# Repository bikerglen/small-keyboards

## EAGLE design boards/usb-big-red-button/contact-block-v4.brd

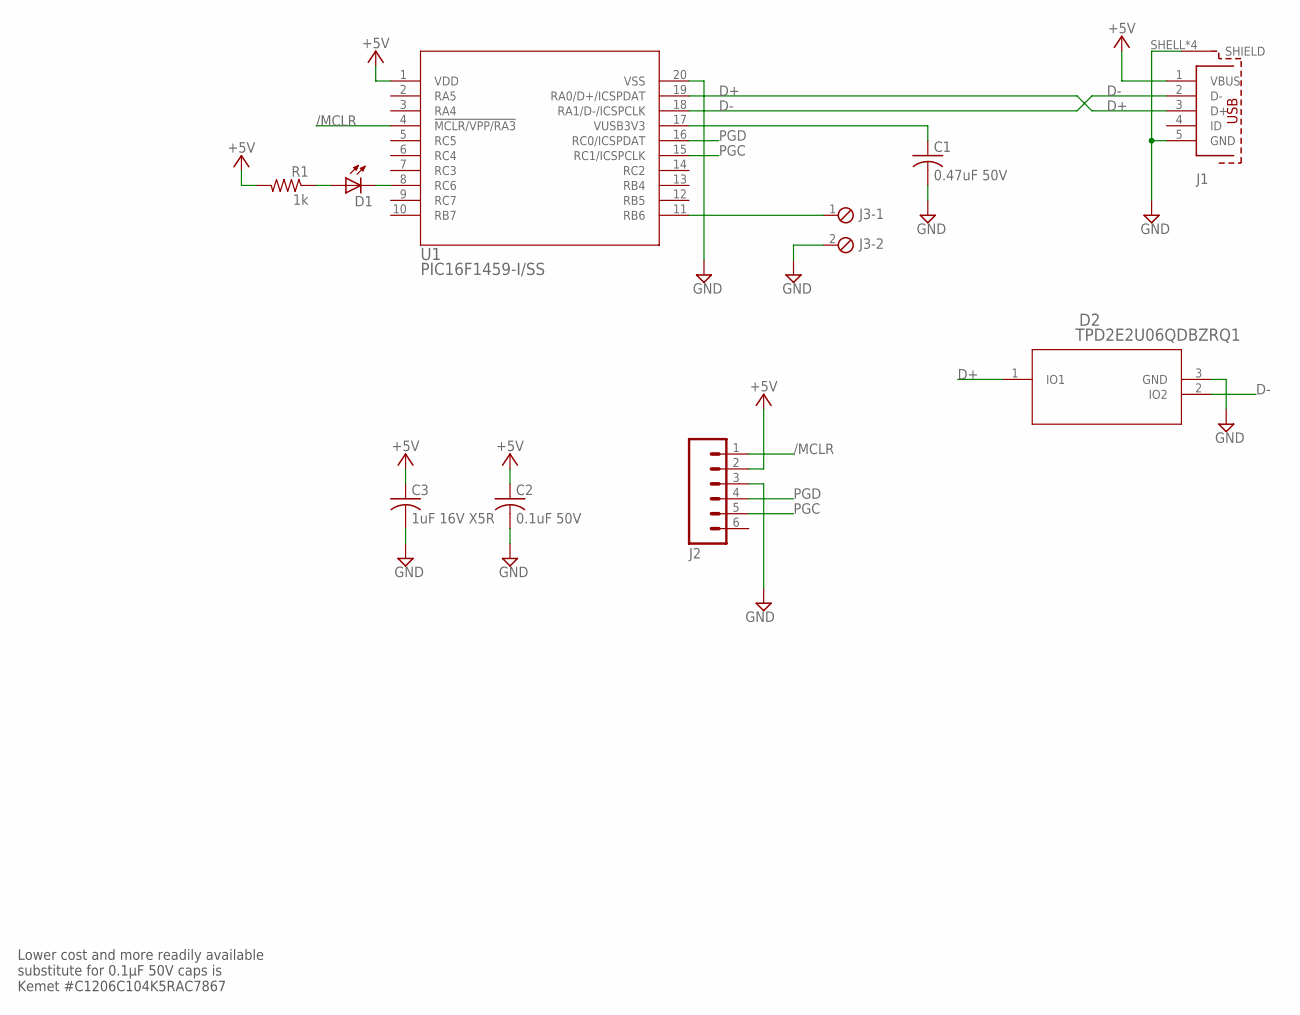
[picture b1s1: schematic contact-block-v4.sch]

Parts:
C1: 0.47uF 50V; C1206K; MFR_PART_NO C1206C474K5RACTU
C2: 0.1uF 50V; C1206K; MFR_PART_NO C1206S104M5RACTU
C3: 1uF 16V X5R; C1210; MFR_PART_NO C1210C105K4PACTU
D1: LEDKA-3528ASYC; KA-3528ASYC
D2: TPD2E2U06QDBZRQ1; DBZ3
J1: 629105136821
J2: M06SIP; 1X06
J3: MPT2; 2POL254
R1: 1k; R1206; MFR_PART_NO CR1206-JW-102ELF
U1: PIC16F1459-I/SS; SSOP20_MC

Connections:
+5V: C2.1, C3.1, J1.1 (VBUS), J2.2, R1.2, U1.1 (VDD)
/MCLR: J2.1, U1.4 (!MCLR/VPP/RA3)
D+: D2.1 (IO1), J1.3 (D+), U1.19 (RA0/D+/ICSPDAT)
D-: D2.2 (IO2), J1.2 (D-), U1.18 (RA1/D-/ICSPCLK)
GND: C1.2, C2.2, C3.2, D2.3 (GND), J1.5 (GND), J1.SHELL (SHIELD), J1.SHELL1 (SHIELD), J1.SHELL2 (SHIELD), J1.SHELL3 (SHIELD), J2.3, J3.2, U1.20 (VSS)
unnamed: D1.A, R1.1
PGC: J2.5, U1.15 (RC1/ICSPCLK)
PGD: J2.4, U1.16 (RC0/ICSPDAT)
RB6: J3.1, U1.11 (RB6)
RC6: D1.C, U1.8 (RC6)
VUSB: C1.1, U1.17 (VUSB3V3)

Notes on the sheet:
Lower cost and more readily available substitute for 0.1µF 50V caps is Kemet #C1206C104K5RAC7867

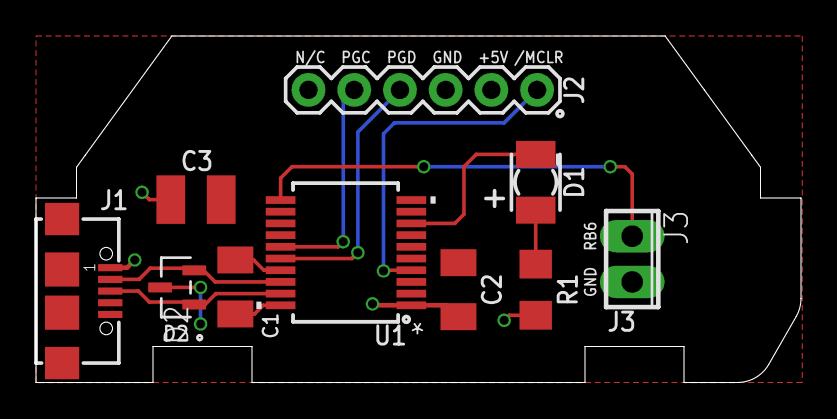
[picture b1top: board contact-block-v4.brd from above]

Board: 2 copper layers, 42.5 x 19.2 mm, 10 parts (0 on the bottom side), 11 nets.

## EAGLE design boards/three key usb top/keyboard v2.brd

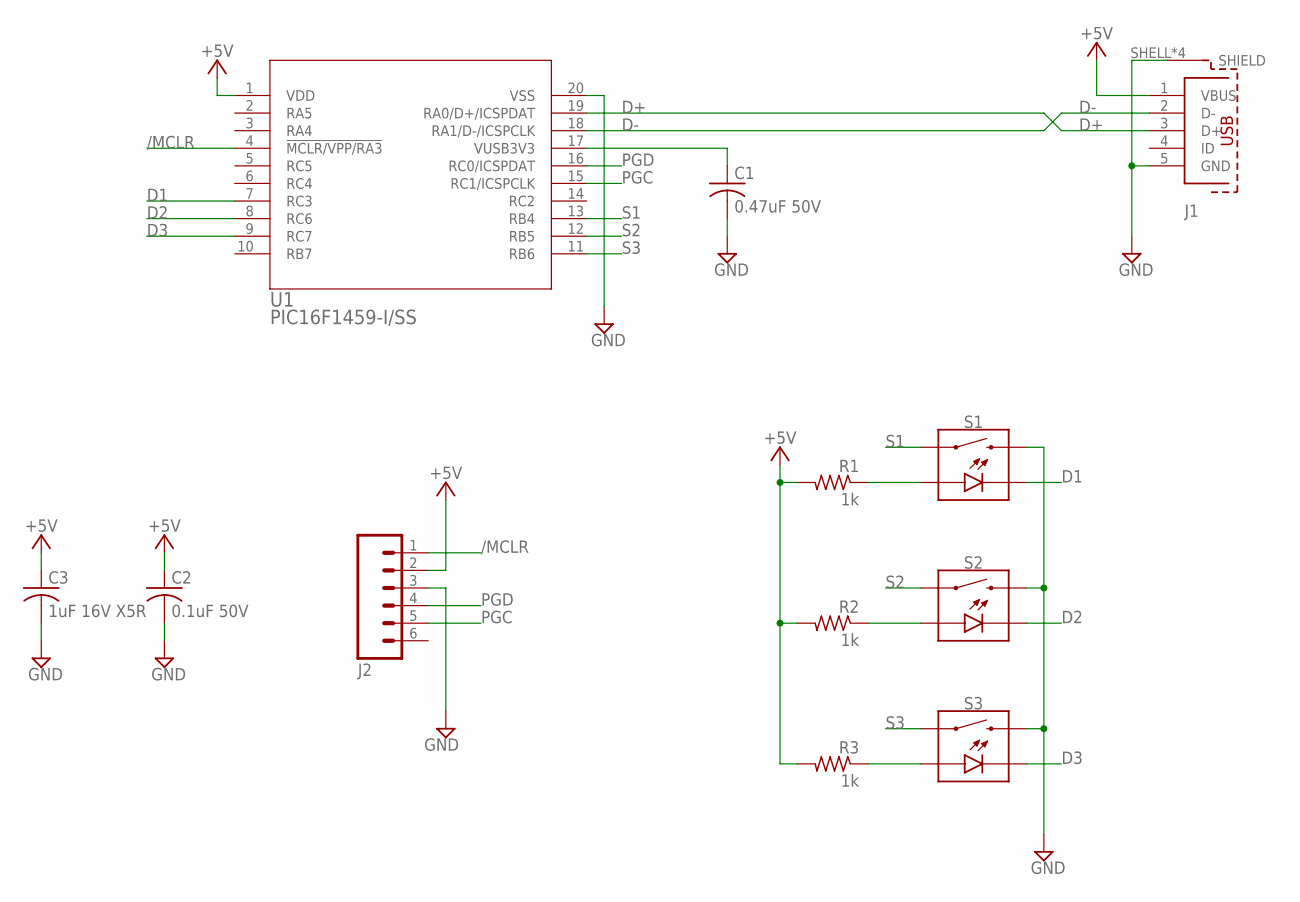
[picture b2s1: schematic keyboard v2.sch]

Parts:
C1: 0.47uF 50V; C1206K; MFR_PART_NO C1206C474K5RACTU
C2: 0.1uF 50V; C1206K; MFR_PART_NO C1206S104M5RACTU
C3: 1uF 16V X5R; C1210; MFR_PART_NO C1210C105K4PACTU
J1: 629105136821
J2: M06SIP; 1X06
R1, R2, R3: 1k; R1206; MFR_PART_NO CR1206-JW-102ELF
S1, S2, S3: MOMENTARY-SWITCH-SPST-LED-PTH-CHERRY; CHERRY-MX-LED
U1: PIC16F1459-I/SS; SSOP20_MC

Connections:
+5V: C2.1, C3.1, J1.1 (VBUS), J2.2, R1.2, R2.2, R3.2, U1.1 (VDD)
/MCLR: J2.1, U1.4 (!MCLR/VPP/RA3)
D1: S1.K (C), U1.7 (RC3)
D2: S2.K (C), U1.8 (RC6)
D3: S3.K (C), U1.9 (RC7)
D+: J1.3 (D+), U1.19 (RA0/D+/ICSPDAT)
D-: J1.2 (D-), U1.18 (RA1/D-/ICSPCLK)
GND: C1.2, C2.2, C3.2, J1.5 (GND), J1.SHELL (SHIELD), J1.SHELL1 (SHIELD), J1.SHELL2 (SHIELD), J1.SHELL3 (SHIELD), J2.3, S1.S2 (2), S2.S2 (2), S3.S2 (2), U1.20 (VSS)
unnamed: R1.1, S1.A
unnamed: R2.1, S2.A
unnamed: R3.1, S3.A
PGC: J2.5, U1.15 (RC1/ICSPCLK)
PGD: J2.4, U1.16 (RC0/ICSPDAT)
S1: S1.S1 (1), U1.13 (RB4)
S2: S2.S1 (1), U1.12 (RB5)
S3: S3.S1 (1), U1.11 (RB6)
VUSB: C1.1, U1.17 (VUSB3V3)

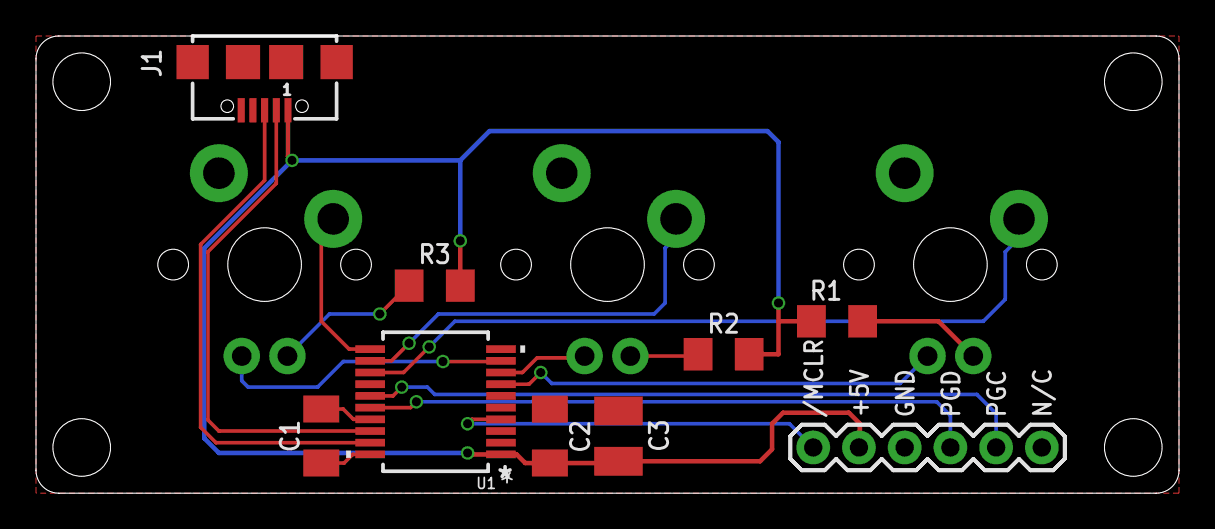
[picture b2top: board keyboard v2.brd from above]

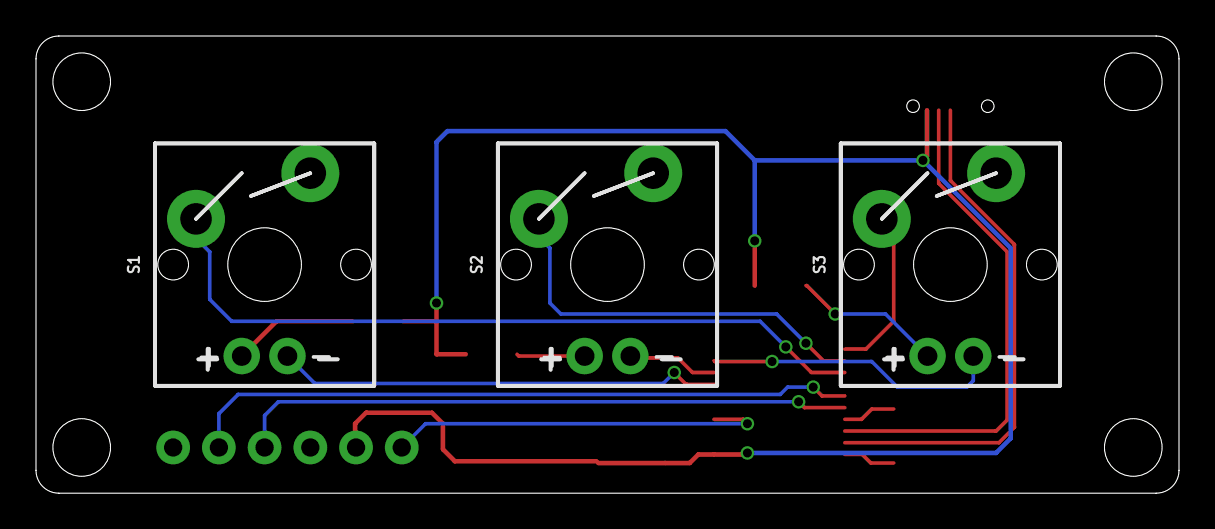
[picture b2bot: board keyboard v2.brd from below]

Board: 2 copper layers, 63.5 x 25.4 mm, 12 parts (3 on the bottom side), 17 nets.

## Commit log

2018-05-11 initial checkin of boards and enclosures
2018-05-11 added note re: screw sizes and tolerances
2018-05-11 fixed spelling
2018-05-11 initial checkin of non-bootloader version of sw
2018-05-11 added prebuilt hex file for programming
2018-12-05 added bootloader version; code is identical except for a few linker options
2019-03-13 initial checkin of USB CDC code to control three LEDs
2019-03-13 bootloader source and build
2020-11-28 added boards for big red usb button contact block mount
2020-11-28 added 3d bits, fusion 360 archive file

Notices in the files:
parts and their libraries:
InputOutputIO: Copyright: Würth Elektronik
SparkFun-Connectors: Licensing: Creative Commons ShareAlike 4.0 International - https://creativecommons.org/licenses/by-sa/4.0
